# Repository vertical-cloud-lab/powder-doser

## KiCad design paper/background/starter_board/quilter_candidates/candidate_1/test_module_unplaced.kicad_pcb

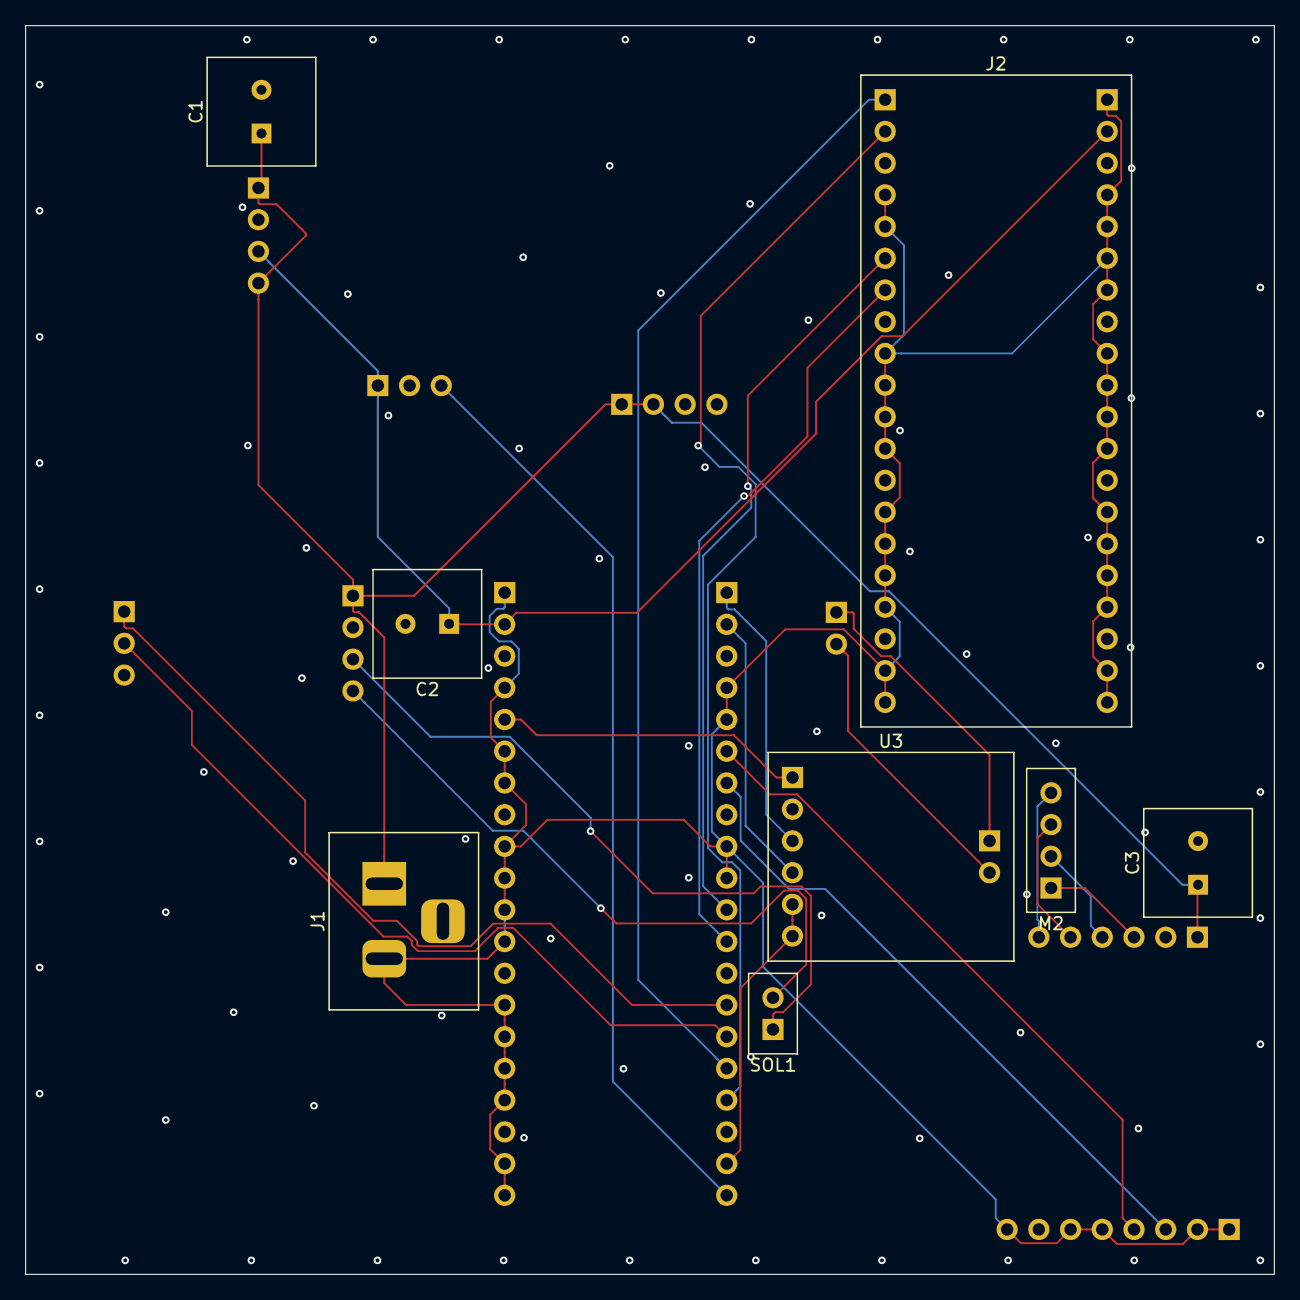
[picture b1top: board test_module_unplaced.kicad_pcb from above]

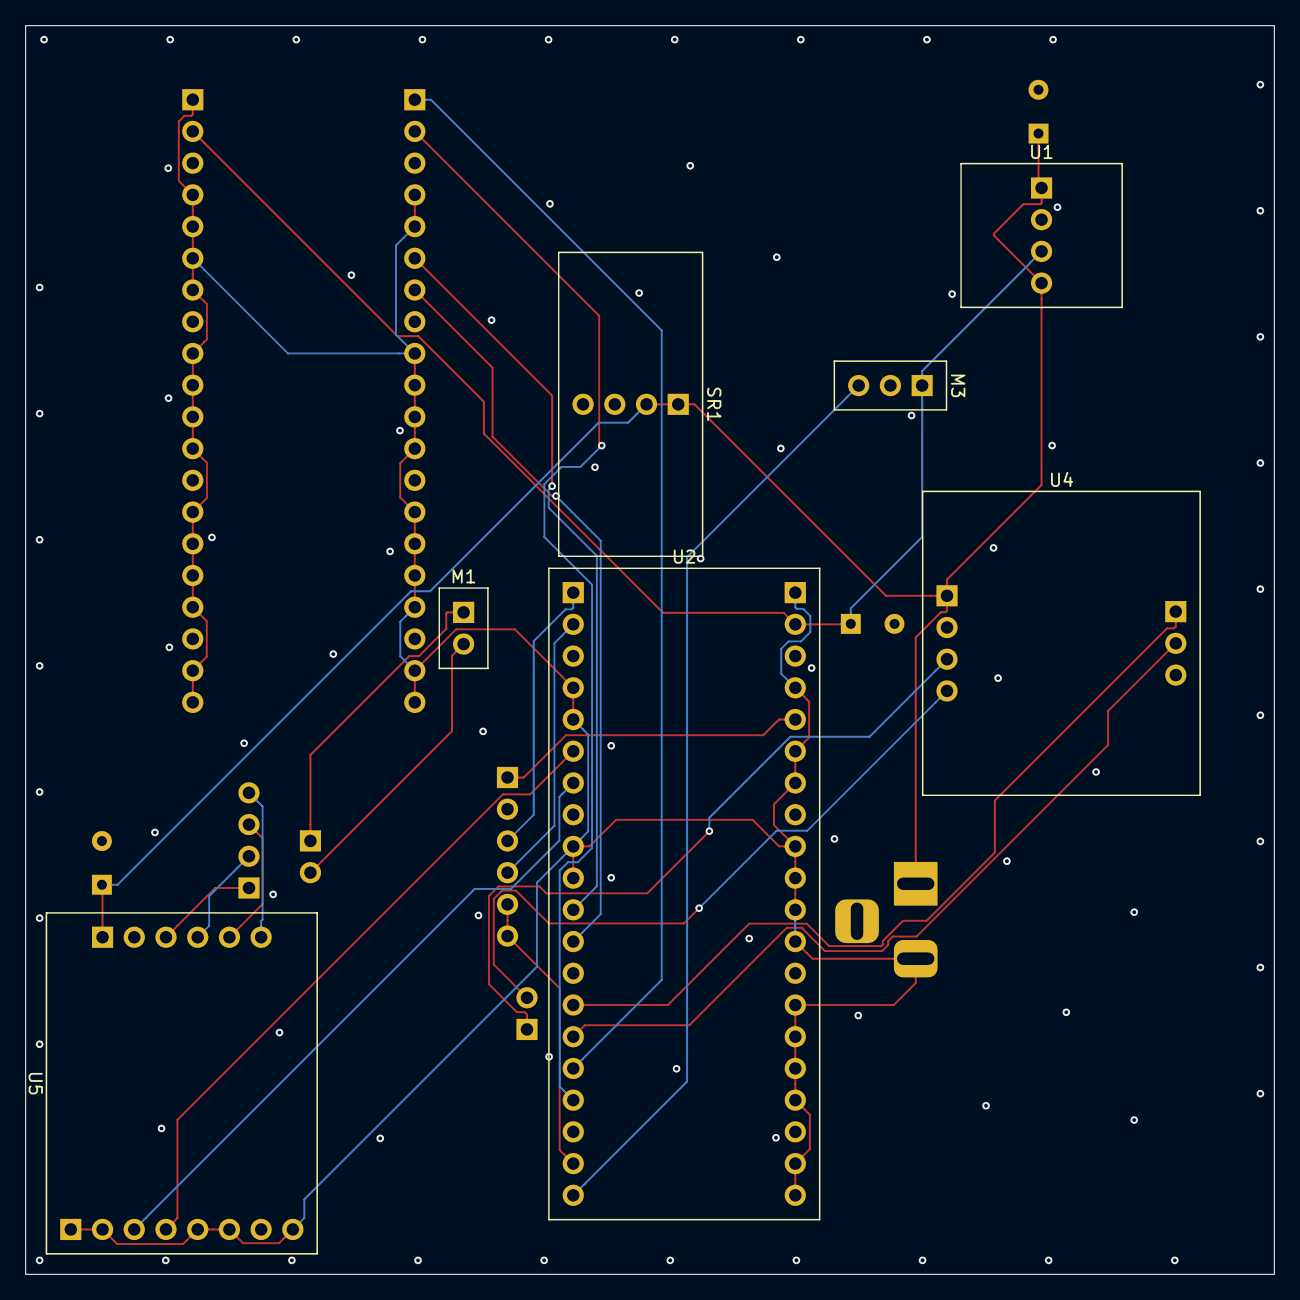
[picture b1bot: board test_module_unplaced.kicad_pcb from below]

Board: 4 copper layers, 100.0 x 100.0 mm, 15 parts (7 on the bottom side), 24 nets.

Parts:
C1, C2, C3: Cap_Polar; CP_Radial_D8.0mm_P3.50mm
J1: Barrel_Jack_12V; BarrelJack_Horizontal
J2: RS232_2CH_Module
M1: ERM_Motor; PinHeader_1x02_P2.54mm_Vertical
M2: Stepper_4wire; PinHeader_1x04_P2.54mm_Vertical
M3: Servo_3pin; PinHeader_1x03_P2.54mm_Vertical
SOL1: Solenoid; PinHeader_1x02_P2.54mm_Vertical
SR1: Shunt_Regulator
U1: D24V22F5_Buck
U2: Pi_Pico_W
U3: DRV2605L_Breakout
U4: DRV8871_Breakout
U5: Tic_T500

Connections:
+3V3: U2.25 (3V3), U3.1 (VIN)
+5V: C2.1 (+), J2.22 (VSYS), M3.1 (+5V), U1.3 (VOUT), U2.22 (VSYS)
+12V: C1.1 (+), C3.1 (+), J1.1 (+12V), SR1.1 (A), SR1.2 (+), U1.1 (VIN), U1.4 (SHDN), U4.1 (VM), U5.9 (VIN)
GND: C1.2 (-), C2.2 (-), C3.2 (-), J1.2 (GND), J2.3 (GND), J2.8 (GND), J2.13 (GND), J2.18 (GND), J2.23 (GND), J2.28 (GND), J2.33 (GND), J2.38 (GND), M3.2 (GND), SR1.3 (B), SR1.4 (-), U1.2 (GND), U2.3 (GND), U2.8 (GND), U2.13 (GND), U2.18 (GND), U2.23 (GND), U2.28 (GND), U2.33 (GND), U2.38 (GND), U3.2 (GND), U4.2 (GND), U4.7 (GND), U5.7 (GND), U5.10 (GND)
HAPT_EN: U2.19 (GP14), U3.5 (IN_TRIG), U3.6 (EN)
I2C_SCL: U2.2 (GP1), U3.4 (SCL)
I2C_SDA: U2.1 (GP0), U3.3 (SDA)
RS232_0_RXD: J2.2 (GP1), U2.17 (GP13)
RS232_0_TXD: J2.1 (GP0), U2.16 (GP12)
RS232_1_RXD: J2.7 (GP5), U2.12 (GP9)
RS232_1_TXD: J2.6 (GP4), U2.11 (GP8)
SERVO_SIG: M3.3 (SIG), U2.20 (GP15)
SOL_A: SOL1.1 (+), U4.3 (OUT1)
SOL_B: SOL1.2 (-), U4.4 (OUT2)
SOL_IN1: U2.14 (GP10), U4.5 (IN1)
SOL_IN2: U2.15 (GP11), U4.6 (IN2)
STP_A1: M2.1 (A1), U5.11 (A1)
STP_A2: M2.2 (A2), U5.12 (A2)
STP_B1: M2.3 (B1), U5.13 (B1)
STP_B2: M2.4 (B2), U5.14 (B2)
STP_RX: U2.7 (GP5), U5.3 (TX)
STP_TX: U2.6 (GP4), U5.4 (RX)
VIB_A: M1.1 (+), U3.7 (OUT+)
VIB_B: M1.2 (-), U3.8 (OUT-)
